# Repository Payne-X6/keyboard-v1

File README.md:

# Custom keyboard

## Preview

You can find full [preview here](https://kicanvas.org/?repo=https%3A%2F%2Fgithub.com%2FPayne-X6%2Fkeyboard-v1%2Ftree%2Fmain%2Fpcb).

** In progress **

## Plate

- Foam PCB mute cotton for MX switches 
  https://www.amazon.co.uk/dp/B0BQQXK8NQ?keywords=poron+plate+foam&dib_tag=se&language=en_US&dib=eyJ2IjoiMSJ9.XYTNvUDawlxtflUTtNRvAJAHrB2GyX2Fe9Aap05gVpjHtK-VWHLtsfrwBhJo4BKF_Q4_FwWimEspIYG0NTUs6LDoDrTVp_xeQT9kImG8Yk1co3-iVW3DoMi6Fy2fW0gjjml-HvBnuYIeeCbBHk2Pzet3BeNR37HN-hVctuZRqW5YEwI7iN2vN7AbP8j_FZBNCFFI7g9Q94T3R2CSMsA5T3lgGgLKhvea0vzh2NFJKhPKjz-lV6NK8QNWQCjud9c1XOCJeVlAkE84srGUMCYMGhTLLkliNjfLdahx9b873sI.yt2VdlyWFnWX5Eu3Ued2DMhH8hzNneoNtG4EgTNmDik&sr=8-2&linkCode=gg2&linkId=32b271488f7a1cf3d70243bb0865cb4d&tag=joescotto-20

## Keycaps
### LPF

- 1 x 1 -    83x
- 2 x 1 -     1x
- 1 x 2 -     2x
- 1.25 x 1 - 10x
- 4.75 x 1 -  1x

### Flat

- 1 x 1 - 12x

## Switches

- Main 97x - Cherry MX xyz (tactile)
- Multimedia 12x - Kailh Choc V2 Low Profile Switch Brown (tactile)

## Sockets

- Kailh MX HotSwap - https://42keebs.eu/shop/parts/kailh-mx-hot-swap-sockets/

## Roller

- EVQWGD001
- THQWGD001

## Knob

## PCB
### MCU

- STM32F072CBTx

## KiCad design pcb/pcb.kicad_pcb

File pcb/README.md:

Visit https://kicanvas.org/?repo=https%3A%2F%2Fgithub.com%2FPayne-X6%2Fkeyboard-v1

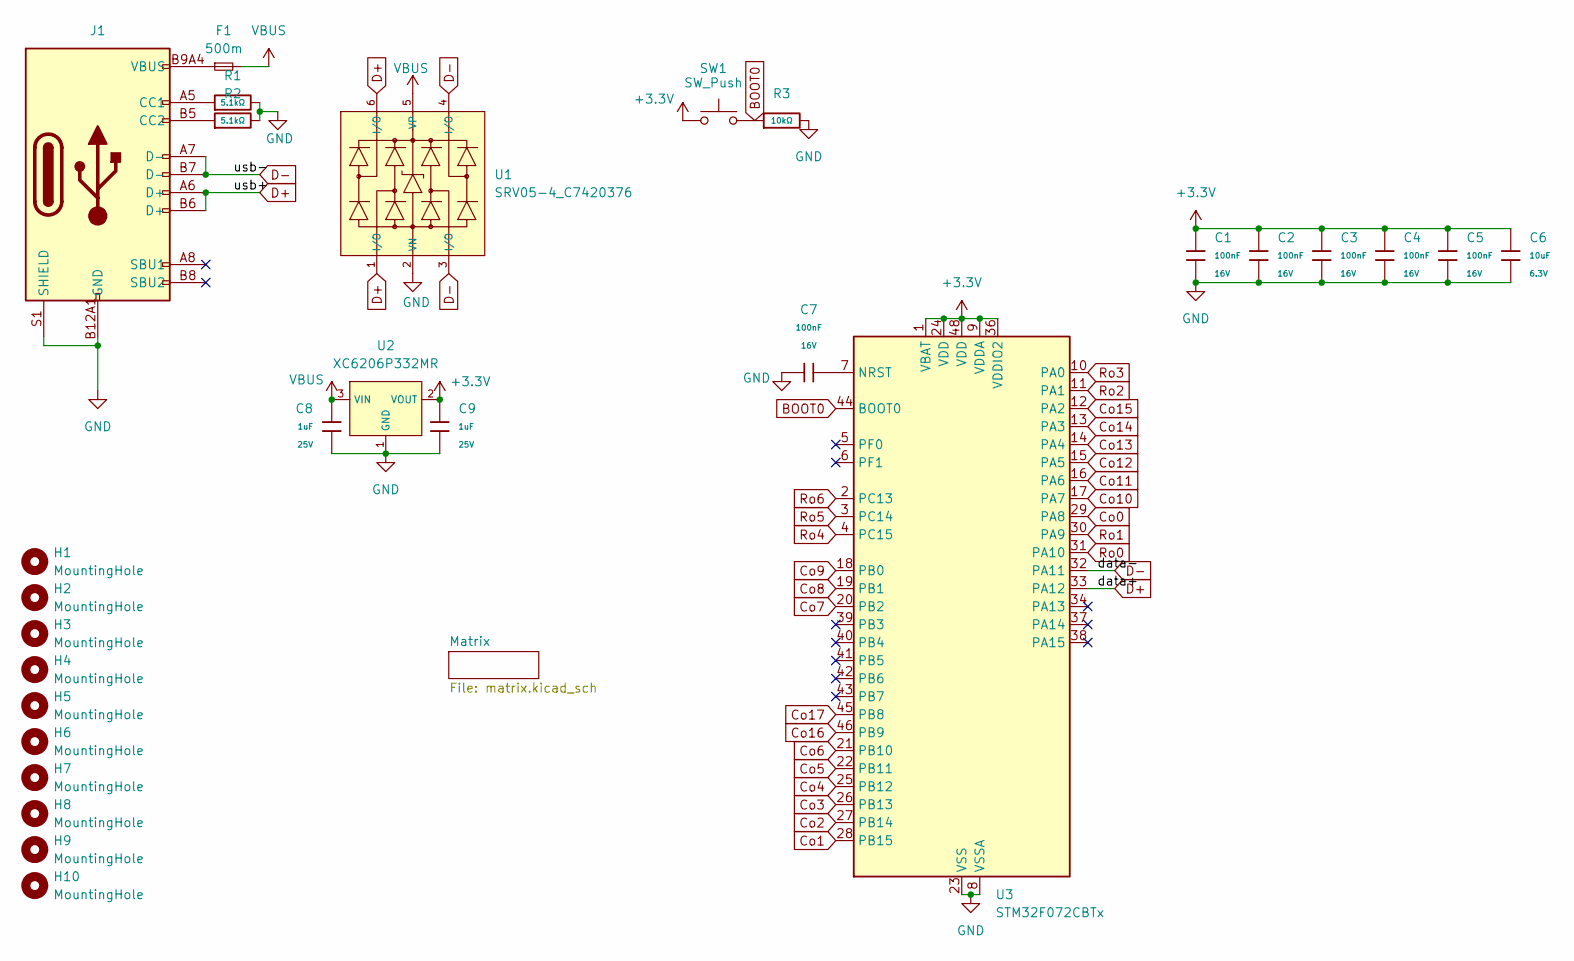
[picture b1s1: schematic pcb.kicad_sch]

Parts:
C1, C2, C3, C4, C5, C7: 100nF; C_0402; Voltage Rated 16V; Tolerance ±10%; Part CL05B104KO5NNNC; LCSC C1525
C6: 10uF; C_0402; Voltage Rated 6.3V; Tolerance ±20%; Part CL05A106MQ5NUNC; LCSC C15525
C8, C9: 1uF; C_0402; Voltage Rated 25V; Tolerance ±10%; Part CL05A105KA5NQNC; LCSC C52923
F1: 500m; Fuse_0603_1608Metric
H1, H2, H3, H4, H5, H6, H7, H8, H9, H10: MountingHole; MountingHole_2mm
J1: Connector, USB-TYPE-C-16P; TYPE-C-SMD_HX-TYPE-C-16PIN; LCSC C2927039
R1, R2: 5.1kΩ; R_0402; Overload Voltage (Max) 50V; Tolerance ±1%; Part 0402WGF5101TCE; LCSC C25905
R3: 10kΩ; R_0402; Overload Voltage (Max) 50V; Tolerance ±1%; Part 0402WGF1002TCE; LCSC C25744
SW1: SW_Push; SW_SPST_SKQG_WithStem; LCSC C115351
U1: SRV05-4_C7420376; SOT-23-6_L2.9-W1.6-P0.95-LS2.8-BL-1; Breakdown Voltage (Vbr) 6V; Clamping Voltage@Ipp 12.5V; Part SRV05-4; LCSC C7420376
U2: XC6206P332MR; SOT-23-3_L2.9-W1.6-P1.90-LS2.8-BR; Output Voltage 3.3V; Dropout Voltage 680mV@(100mA); Part XC6206P332MR-G; LCSC C5446
U3: STM32F072CBTx; LQFP-48_7x7mm_P0.5mm

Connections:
+3.3V: C1.2, C2.2, C3.2, C4.2, C5.2, C6.1, C9.1, SW1.1, U2.2 (VOUT), U3.1 (VBAT), U3.9 (VDDA), U3.24 (VDD), U3.36 (VDDIO2), U3.48 (VDD)
BOOT0: R3.1, SW1.2, U3.44 (BOOT0)
Co0: U3.29 (PA8); also elsewhere on the board
Co1: U3.28 (PB15); also elsewhere on the board
Co2: U3.27 (PB14); also elsewhere on the board
Co3: U3.26 (PB13); also elsewhere on the board
Co4: U3.25 (PB12); also elsewhere on the board
Co5: U3.22 (PB11); also elsewhere on the board
Co6: U3.21 (PB10); also elsewhere on the board
Co7: U3.20 (PB2); also elsewhere on the board
Co8: U3.19 (PB1); also elsewhere on the board
Co9: U3.18 (PB0); also elsewhere on the board
Co10: U3.17 (PA7); also elsewhere on the board
Co11: U3.16 (PA6); also elsewhere on the board
Co12: U3.15 (PA5); also elsewhere on the board
Co13: U3.14 (PA4); also elsewhere on the board
Co14: U3.13 (PA3); also elsewhere on the board
Co15: U3.12 (PA2); also elsewhere on the board
Co16: U3.46 (PB9); also elsewhere on the board
Co17: U3.45 (PB8); also elsewhere on the board
D+: J1.A6 (D+), J1.B6 (D+), U1.1 (I/O), U1.6 (I/O), U3.33 (PA12)
D-: J1.A7 (D-), J1.B7 (D-), U1.3 (I/O), U1.4 (I/O), U3.32 (PA11)
GND: C1.1, C2.1, C3.1, C4.1, C5.1, C6.2, C7.1, C8.2, C9.2, J1.A12B1 (GND), J1.B12A1 (GND), J1.S1 (SHIELD), R1.2, R2.2, R3.2, U1.2 (VN), U2.1 (GND), U3.8 (VSSA), U3.23 (VSS), U3.35 (VSS), U3.47 (VSS)
unnamed: F1.1, J1.A9B4 (VBUS), J1.B9A4 (VBUS)
unnamed: J1.A5 (CC1), R1.1
unnamed: J1.B5 (CC2), R2.1
unnamed: C7.2, U3.7 (NRST)
Ro0: U3.31 (PA10); also elsewhere on the board
Ro1: U3.30 (PA9); also elsewhere on the board
Ro2: U3.11 (PA1); also elsewhere on the board
Ro3: U3.10 (PA0); also elsewhere on the board
Ro4: U3.4 (PC15); also elsewhere on the board
Ro5: U3.3 (PC14); also elsewhere on the board
Ro6: U3.2 (PC13); also elsewhere on the board
VBUS: C8.1, F1.2, U1.5 (VP), U2.3 (VIN)

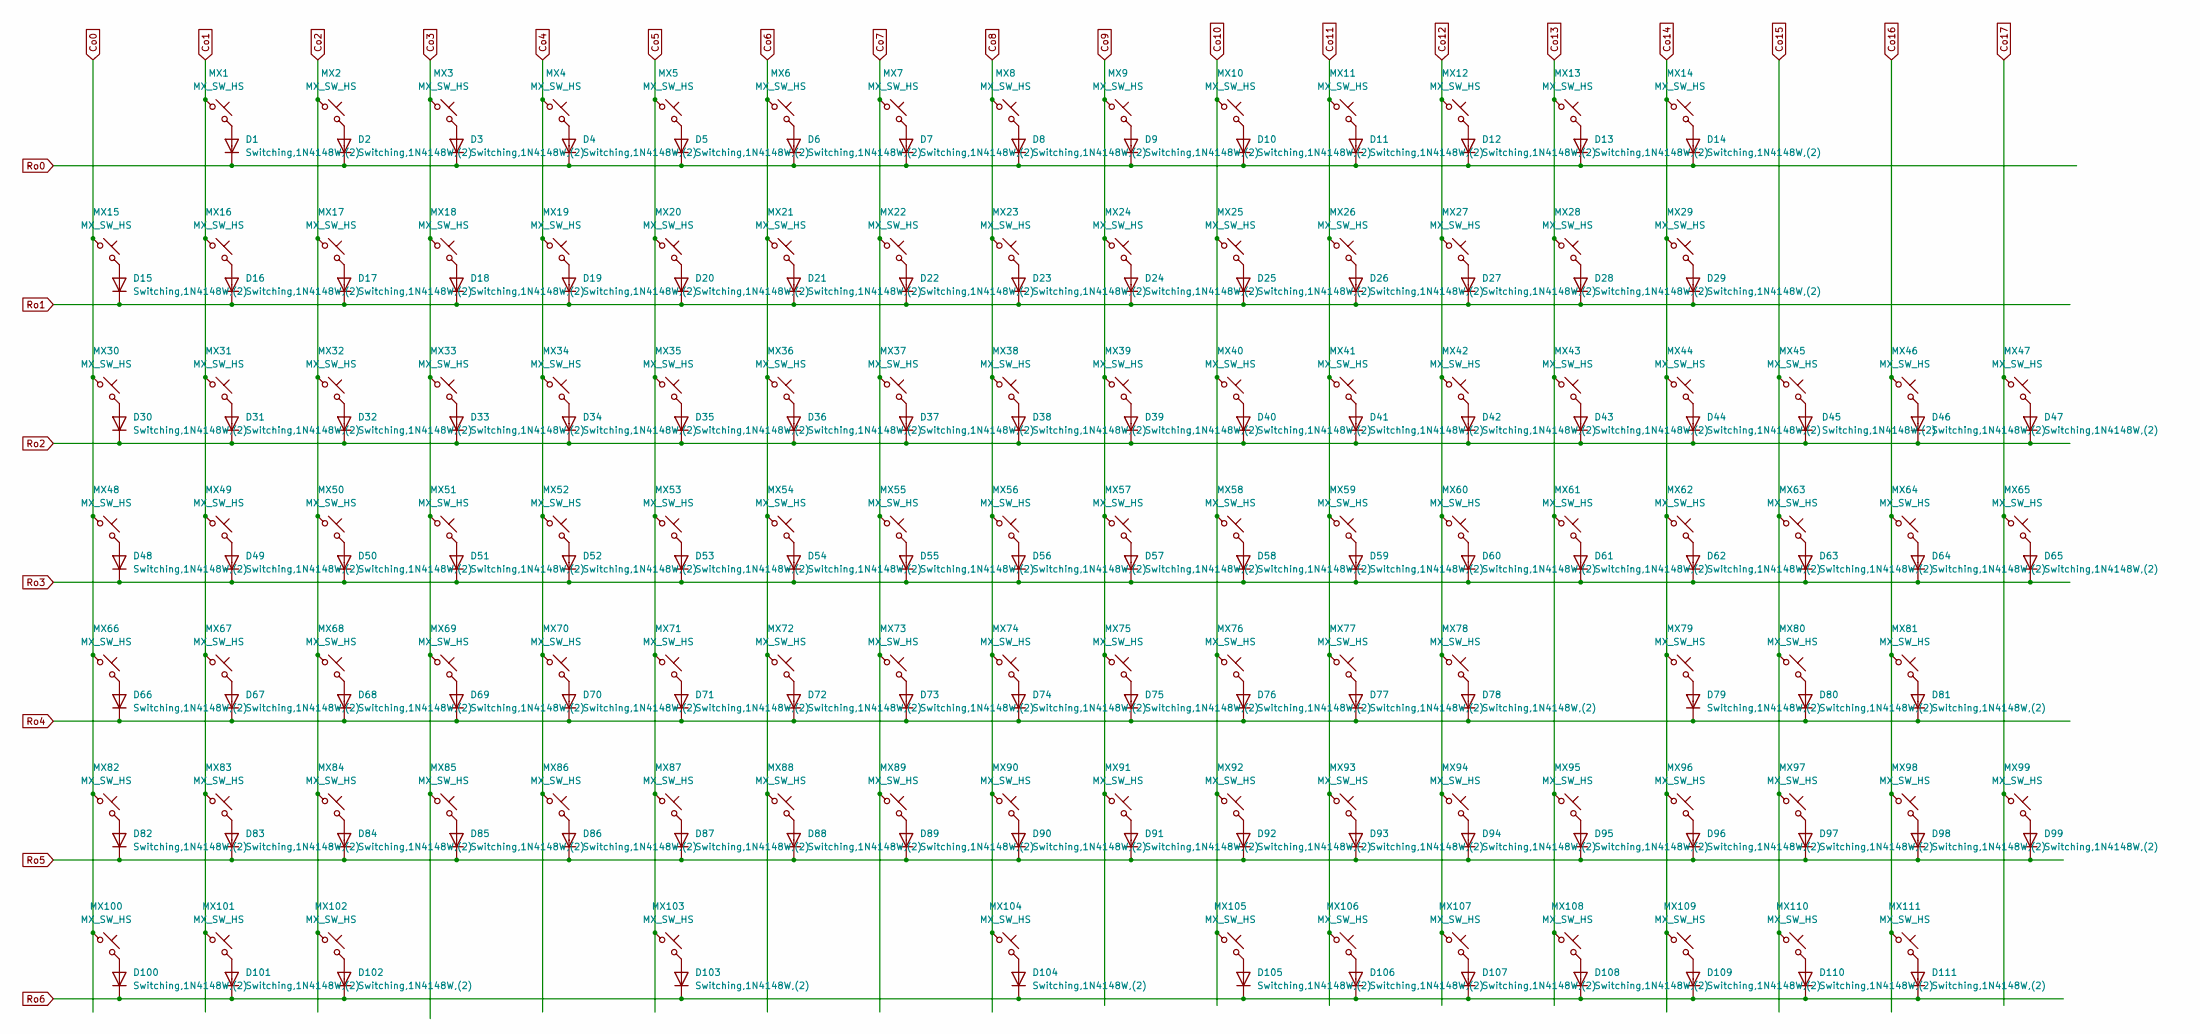
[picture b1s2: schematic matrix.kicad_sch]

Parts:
D1, D2, D3, D4, D5, D6, D7, D8, D9, D10, D11, D12, D13, D14, D15, D16, D17, D18, D19, D20, D21, D22, D23, D24, D25, D26, D27, D28, D29, D30, D31, D32, D33, D34, D35, D36, D37, D38, D39, D40, D41, D42, D43, D44, D45, D46, D47, D48, D49, D50, D51, D52, D53, D54, D55, D56, D57, D58, D59, D60, D61, D62, D63, D64, D65, D66, D67, D68, D69, D70, D71, D72, D73, D74, D75, D76, D77, D78, D79, D80, D81, D82, D83, D84, D85, D86, D87, D88, D89, D90, D91, D92, D93, D94, D95, D96, D97, D98, D99, D100, D101, D102, D103, D104, D105, D106, D107, D108, D109, D110, D111: Switching,1N4148W,(2); D_SOD-123
MX1, MX2, MX3, MX4, MX5, MX6, MX7, MX8, MX9, MX10, MX11, MX12, MX13, MX14, MX15, MX16, MX17, MX18, MX19, MX20, MX21, MX22, MX23, MX24, MX25, MX26, MX27, MX28, MX29, MX30, MX31, MX32, MX33, MX34, MX35, MX36, MX37, MX38, MX39, MX40, MX41, MX42, MX44, MX45, MX46, MX47, MX49, MX50, MX51, MX52, MX53, MX54, MX55, MX56, MX57, MX58, MX59, MX60, MX61, MX62, MX63, MX64, MX65, MX67, MX68, MX69, MX70, MX71, MX72, MX73, MX74, MX75, MX76, MX77, MX78, MX79, MX80, MX81, MX83, MX84, MX85, MX86, MX87, MX88, MX89, MX90, MX91, MX92, MX93, MX94, MX95, MX96, MX97, MX98, MX99, MX103, MX107, MX108, MX109, MX110, MX111: MX_SW_HS; SW_MX_HS_CPG151101S11_1u
MX43, MX48, MX66, MX82, MX100, MX101, MX102, MX104, MX105, MX106: MX_SW_HS; SW_MX_HS_CPG151101S11_1.25u

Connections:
Co0: MX15.1, MX30.1, MX48.1, MX66.1, MX82.1, MX100.1; also elsewhere on the board
Co1: MX1.1, MX16.1, MX31.1, MX49.1, MX67.1, MX83.1, MX101.1; also elsewhere on the board
Co2: MX2.1, MX17.1, MX32.1, MX50.1, MX68.1, MX84.1, MX102.1; also elsewhere on the board
Co3: MX3.1, MX18.1, MX33.1, MX51.1, MX69.1, MX85.1; also elsewhere on the board
Co4: MX4.1, MX19.1, MX34.1, MX52.1, MX70.1, MX86.1; also elsewhere on the board
Co5: MX5.1, MX20.1, MX35.1, MX53.1, MX71.1, MX87.1, MX103.1; also elsewhere on the board
Co6: MX6.1, MX21.1, MX36.1, MX54.1, MX72.1, MX88.1; also elsewhere on the board
Co7: MX7.1, MX22.1, MX37.1, MX55.1, MX73.1, MX89.1; also elsewhere on the board
Co8: MX8.1, MX23.1, MX38.1, MX56.1, MX74.1, MX90.1, MX104.1; also elsewhere on the board
Co9: MX9.1, MX24.1, MX39.1, MX57.1, MX75.1, MX91.1; also elsewhere on the board
Co10: MX10.1, MX25.1, MX40.1, MX58.1, MX76.1, MX92.1, MX105.1; also elsewhere on the board
Co11: MX11.1, MX26.1, MX41.1, MX59.1, MX77.1, MX93.1, MX106.1; also elsewhere on the board
Co12: MX12.1, MX27.1, MX42.1, MX60.1, MX78.1, MX94.1, MX107.1; also elsewhere on the board
Co13: MX13.1, MX28.1, MX43.1, MX61.1, MX95.1, MX108.1; also elsewhere on the board
Co14: MX14.1, MX29.1, MX44.1, MX62.1, MX79.1, MX96.1, MX109.1; also elsewhere on the board
Co15: MX45.1, MX63.1, MX80.1, MX97.1, MX110.1; also elsewhere on the board
Co16: MX46.1, MX64.1, MX81.1, MX98.1, MX111.1; also elsewhere on the board
Co17: MX47.1, MX65.1, MX99.1; also elsewhere on the board
unnamed: D1.2, MX1.2
unnamed: D2.2, MX2.2
unnamed: D3.2, MX3.2
unnamed: D4.2, MX4.2
unnamed: D5.2, MX5.2
unnamed: D6.2, MX6.2
unnamed: D7.2, MX7.2
unnamed: D8.2, MX8.2
unnamed: D9.2, MX9.2
unnamed: D10.2, MX10.2
unnamed: D11.2, MX11.2
unnamed: D12.2, MX12.2
unnamed: D13.2, MX13.2
unnamed: D14.2, MX14.2
unnamed: D15.2, MX15.2
unnamed: D16.2, MX16.2
unnamed: D17.2, MX17.2
unnamed: D18.2, MX18.2
unnamed: D19.2, MX19.2
unnamed: D20.2, MX20.2
unnamed: D21.2, MX21.2
unnamed: D22.2, MX22.2
unnamed: D23.2, MX23.2
unnamed: D24.2, MX24.2
unnamed: D25.2, MX25.2
unnamed: D26.2, MX26.2
unnamed: D27.2, MX27.2
unnamed: D28.2, MX28.2
unnamed: D29.2, MX29.2
unnamed: D30.2, MX30.2
unnamed: D31.2, MX31.2
unnamed: D32.2, MX32.2
unnamed: D33.2, MX33.2
unnamed: D34.2, MX34.2
unnamed: D35.2, MX35.2
unnamed: D36.2, MX36.2
unnamed: D37.2, MX37.2
unnamed: D38.2, MX38.2
unnamed: D39.2, MX39.2
unnamed: D40.2, MX40.2
unnamed: D41.2, MX41.2
unnamed: D42.2, MX42.2
unnamed: D43.2, MX43.2
unnamed: D44.2, MX44.2
unnamed: D45.2, MX45.2
unnamed: D46.2, MX46.2
unnamed: D47.2, MX47.2
unnamed: D48.2, MX48.2
unnamed: D49.2, MX49.2
unnamed: D50.2, MX50.2
unnamed: D51.2, MX51.2
unnamed: D52.2, MX52.2
unnamed: D53.2, MX53.2
unnamed: D54.2, MX54.2
unnamed: D55.2, MX55.2
unnamed: D56.2, MX56.2
unnamed: D57.2, MX57.2
unnamed: D58.2, MX58.2
unnamed: D59.2, MX59.2
unnamed: D60.2, MX60.2
unnamed: D61.2, MX61.2
unnamed: D62.2, MX62.2
unnamed: D63.2, MX63.2
unnamed: D64.2, MX64.2
unnamed: D65.2, MX65.2
unnamed: D66.2, MX66.2
unnamed: D67.2, MX67.2
unnamed: D68.2, MX68.2
unnamed: D69.2, MX69.2
unnamed: D70.2, MX70.2
unnamed: D71.2, MX71.2
unnamed: D72.2, MX72.2
unnamed: D73.2, MX73.2
unnamed: D74.2, MX74.2
unnamed: D75.2, MX75.2
unnamed: D76.2, MX76.2
unnamed: D77.2, MX77.2
unnamed: D78.2, MX78.2
unnamed: D79.2, MX79.2
unnamed: D80.2, MX80.2
unnamed: D81.2, MX81.2
unnamed: D82.2, MX82.2
unnamed: D83.2, MX83.2
unnamed: D84.2, MX84.2
unnamed: D85.2, MX85.2
unnamed: D86.2, MX86.2
unnamed: D87.2, MX87.2
unnamed: D88.2, MX88.2
unnamed: D89.2, MX89.2
unnamed: D90.2, MX90.2
unnamed: D91.2, MX91.2
unnamed: D92.2, MX92.2
unnamed: D93.2, MX93.2
unnamed: D94.2, MX94.2
unnamed: D95.2, MX95.2
unnamed: D96.2, MX96.2
unnamed: D97.2, MX97.2
unnamed: D98.2, MX98.2
unnamed: D99.2, MX99.2
unnamed: D100.2, MX100.2
unnamed: D101.2, MX101.2
unnamed: D102.2, MX102.2
unnamed: D103.2, MX103.2
unnamed: D104.2, MX104.2
unnamed: D105.2, MX105.2
unnamed: D106.2, MX106.2
unnamed: D107.2, MX107.2
unnamed: D108.2, MX108.2
unnamed: D109.2, MX109.2
unnamed: D110.2, MX110.2
unnamed: D111.2, MX111.2
Ro0: D1.1, D2.1, D3.1, D4.1, D5.1, D6.1, D7.1, D8.1, D9.1, D10.1, D11.1, D12.1, D13.1, D14.1; also elsewhere on the board
Ro1: D15.1, D16.1, D17.1, D18.1, D19.1, D20.1, D21.1, D22.1, D23.1, D24.1, D25.1, D26.1, D27.1, D28.1, D29.1; also elsewhere on the board
Ro2: D30.1, D31.1, D32.1, D33.1, D34.1, D35.1, D36.1, D37.1, D38.1, D39.1, D40.1, D41.1, D42.1, D43.1, D44.1, D45.1, D46.1, D47.1; also elsewhere on the board
Ro3: D48.1, D49.1, D50.1, D51.1, D52.1, D53.1, D54.1, D55.1, D56.1, D57.1, D58.1, D59.1, D60.1, D61.1, D62.1, D63.1, D64.1, D65.1; also elsewhere on the board
Ro4: D66.1, D67.1, D68.1, D69.1, D70.1, D71.1, D72.1, D73.1, D74.1, D75.1, D76.1, D77.1, D78.1, D79.1, D80.1, D81.1; also elsewhere on the board
Ro5: D82.1, D83.1, D84.1, D85.1, D86.1, D87.1, D88.1, D89.1, D90.1, D91.1, D92.1, D93.1, D94.1, D95.1, D96.1, D97.1, D98.1, D99.1; also elsewhere on the board
Ro6: D100.1, D101.1, D102.1, D103.1, D104.1, D105.1, D106.1, D107.1, D108.1, D109.1, D110.1, D111.1; also elsewhere on the board

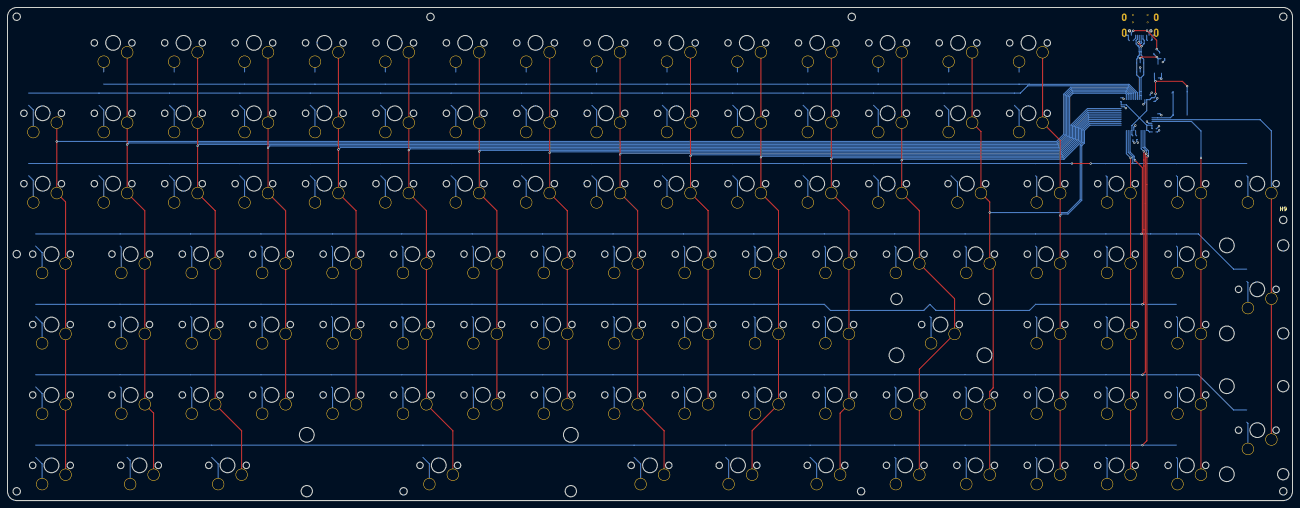
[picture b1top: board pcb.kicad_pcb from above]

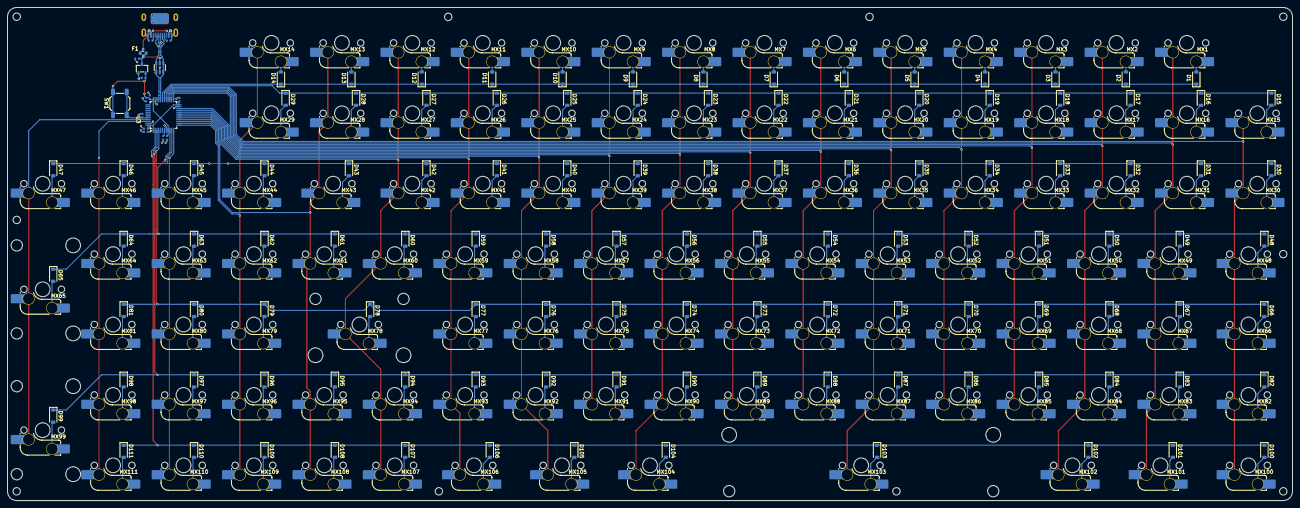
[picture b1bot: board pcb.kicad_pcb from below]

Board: 2 copper layers, 347.7 x 133.4 mm, 250 parts (240 on the bottom side), 146 nets.

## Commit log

2026-03-30 ATmega32U4
2026-03-30 Add link to Kicanvas in README
2026-03-31 rearange repository
2026-03-31 Readme
2026-03-31 New (#1)
    * rearange repository
    * Readme
2026-03-31 change MCU to STM32F0
2026-03-31 fix readme
2026-04-01 ESD protection
2026-04-02 Connecting MCU
2026-04-03 Update MCU datasheet
2026-04-03 Connects all components on the PCB
2026-04-04 Mouting holes
2026-04-04 200 more connections to go
2026-04-04 100 more connections to go
2026-04-04 Matrix ready
2026-04-05 Change generic diodes to SOD-123
    50% done
2026-04-05 finished diodes and finished top MCU datalines
2026-04-05 Add some LSCPCB footprints
2026-04-06 Replace some more with LSCPCB library
2026-04-06 matrix connected
2026-04-06 DRC test
2026-04-06 fix mouting holes
2026-04-06 jlcpcb USB-C
2026-04-07 Before production
2026-04-12 fine tuning
